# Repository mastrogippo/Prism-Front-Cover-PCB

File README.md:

## Front cover for Prism 

[Writeup and pics here](https://www.mastrogippo.it/2019/09/front-cover/)

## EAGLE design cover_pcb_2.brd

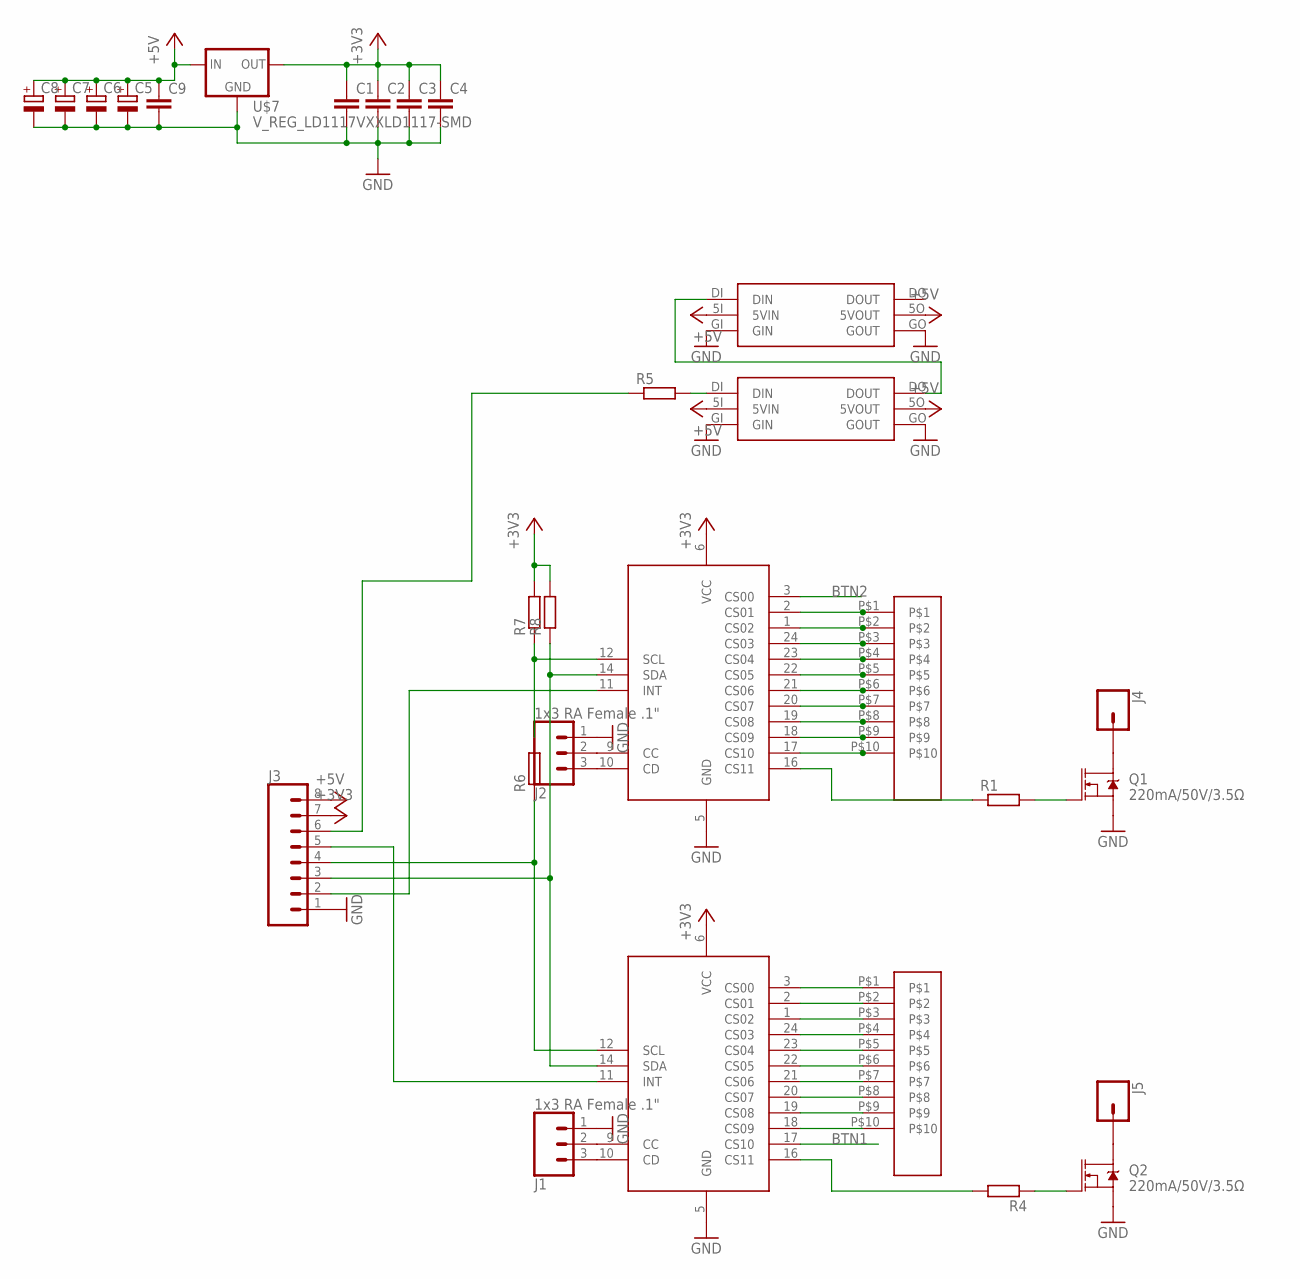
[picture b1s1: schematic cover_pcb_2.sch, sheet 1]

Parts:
C1, C2, C3, C4, C9: C-EUC0805K; C0805K
C5, C6, C7, C8: CPOL-EUSMCD; SMC_D
J1, J2: 1x3 RA Female .1"; 1X03_SMD_RA_FEMALE
J3: CONN_08SMD-MALE; 1X08_SMD_MALE
J4, J5: CONN_01SPRING-CONN; SPRING-CONNECTOR
Q1, Q2: 220mA/50V/3.5Ω; SOT23-3
R1, R4, R5, R6, R7, R8: R-EU_R0805; R0805
U$1, U$2: RGB6LED
U$3, U$4: TOUCH10; TOUCH10CM
U$5, U$6: CP112S; QSOP24
U$7: V_REG_LD1117VXXLD1117-SMD; SOT223

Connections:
+3V3: C1.1, C2.1, C3.1, C4.1, J3.7, R7.2, R8.2, U$5.6 (VCC), U$6.6 (VCC), U$7.2 (OUT)
+5V: C5.+, C6.+, C7.+, C8.+, C9.1, J3.8, U$1.5I (5VIN), U$1.5O (5VOUT), U$2.5I (5VIN), U$2.5O (5VOUT), U$7.3 (IN)
BTN1: U$6.17 (CS10)
BTN2: U$5.3 (CS00)
GND: C1.2, C2.2, C3.2, C4.2, C5.-, C6.-, C7.-, C8.-, C9.2, J1.1, J2.1, J3.1, Q1.2 (S), Q2.2 (S), U$1.GI (GIN), U$1.GO (GOUT), U$2.GI (GIN), U$2.GO (GOUT), U$5.5 (GND), U$6.5 (GND), U$7.1 (GND); also elsewhere on the board
unnamed: U$3.P$1, U$5.2 (CS01)
unnamed: U$3.P$2, U$5.1 (CS02)
unnamed: U$3.P$3, U$5.24 (CS03)
unnamed: U$3.P$4, U$5.23 (CS04)
unnamed: U$3.P$5, U$5.22 (CS05)
unnamed: U$3.P$6, U$5.21 (CS06)
unnamed: U$3.P$7, U$5.20 (CS07)
unnamed: U$3.P$8, U$5.19 (CS08)
unnamed: U$3.P$9, U$5.18 (CS09)
unnamed: U$4.P$1, U$6.3 (CS00)
unnamed: U$4.P$2, U$6.2 (CS01)
unnamed: U$4.P$3, U$6.1 (CS02)
unnamed: U$4.P$4, U$6.24 (CS03)
unnamed: U$4.P$5, U$6.23 (CS04)
unnamed: U$4.P$6, U$6.22 (CS05)
unnamed: U$4.P$7, U$6.21 (CS06)
unnamed: U$4.P$8, U$6.20 (CS07)
unnamed: U$4.P$9, U$6.19 (CS08)
unnamed: U$4.P$10, U$6.18 (CS09)
unnamed: R6.2, R7.1, U$5.12 (SCL)
unnamed: J3.5, U$6.11 (INT)
unnamed: U$1.DI (DIN), U$2.DO (DOUT)
unnamed: R1.1, U$5.16 (CS11)
unnamed: R4.2, U$6.16 (CS11)
unnamed: Q2.1 (G), R4.1
unnamed: J5.P$2, Q2.3 (D)
unnamed: R5.2, U$2.DI (DIN)
unnamed: J3.6, R5.1
unnamed: J3.3, R8.1, U$5.14 (SDA), U$6.14 (SDA)
unnamed: J3.4, R6.1, U$6.12 (SCL)
unnamed: J3.2, U$5.11 (INT)
unnamed: J4.P$2, Q1.3 (D)
unnamed: J2.2, U$5.9 (CC)
unnamed: J2.3, U$5.10 (CD)
unnamed: J1.2, U$6.9 (CC)
unnamed: J1.3, U$6.10 (CD)
unnamed: Q1.1 (G), R1.2
T1: U$3.P$10, U$5.17 (CS10)

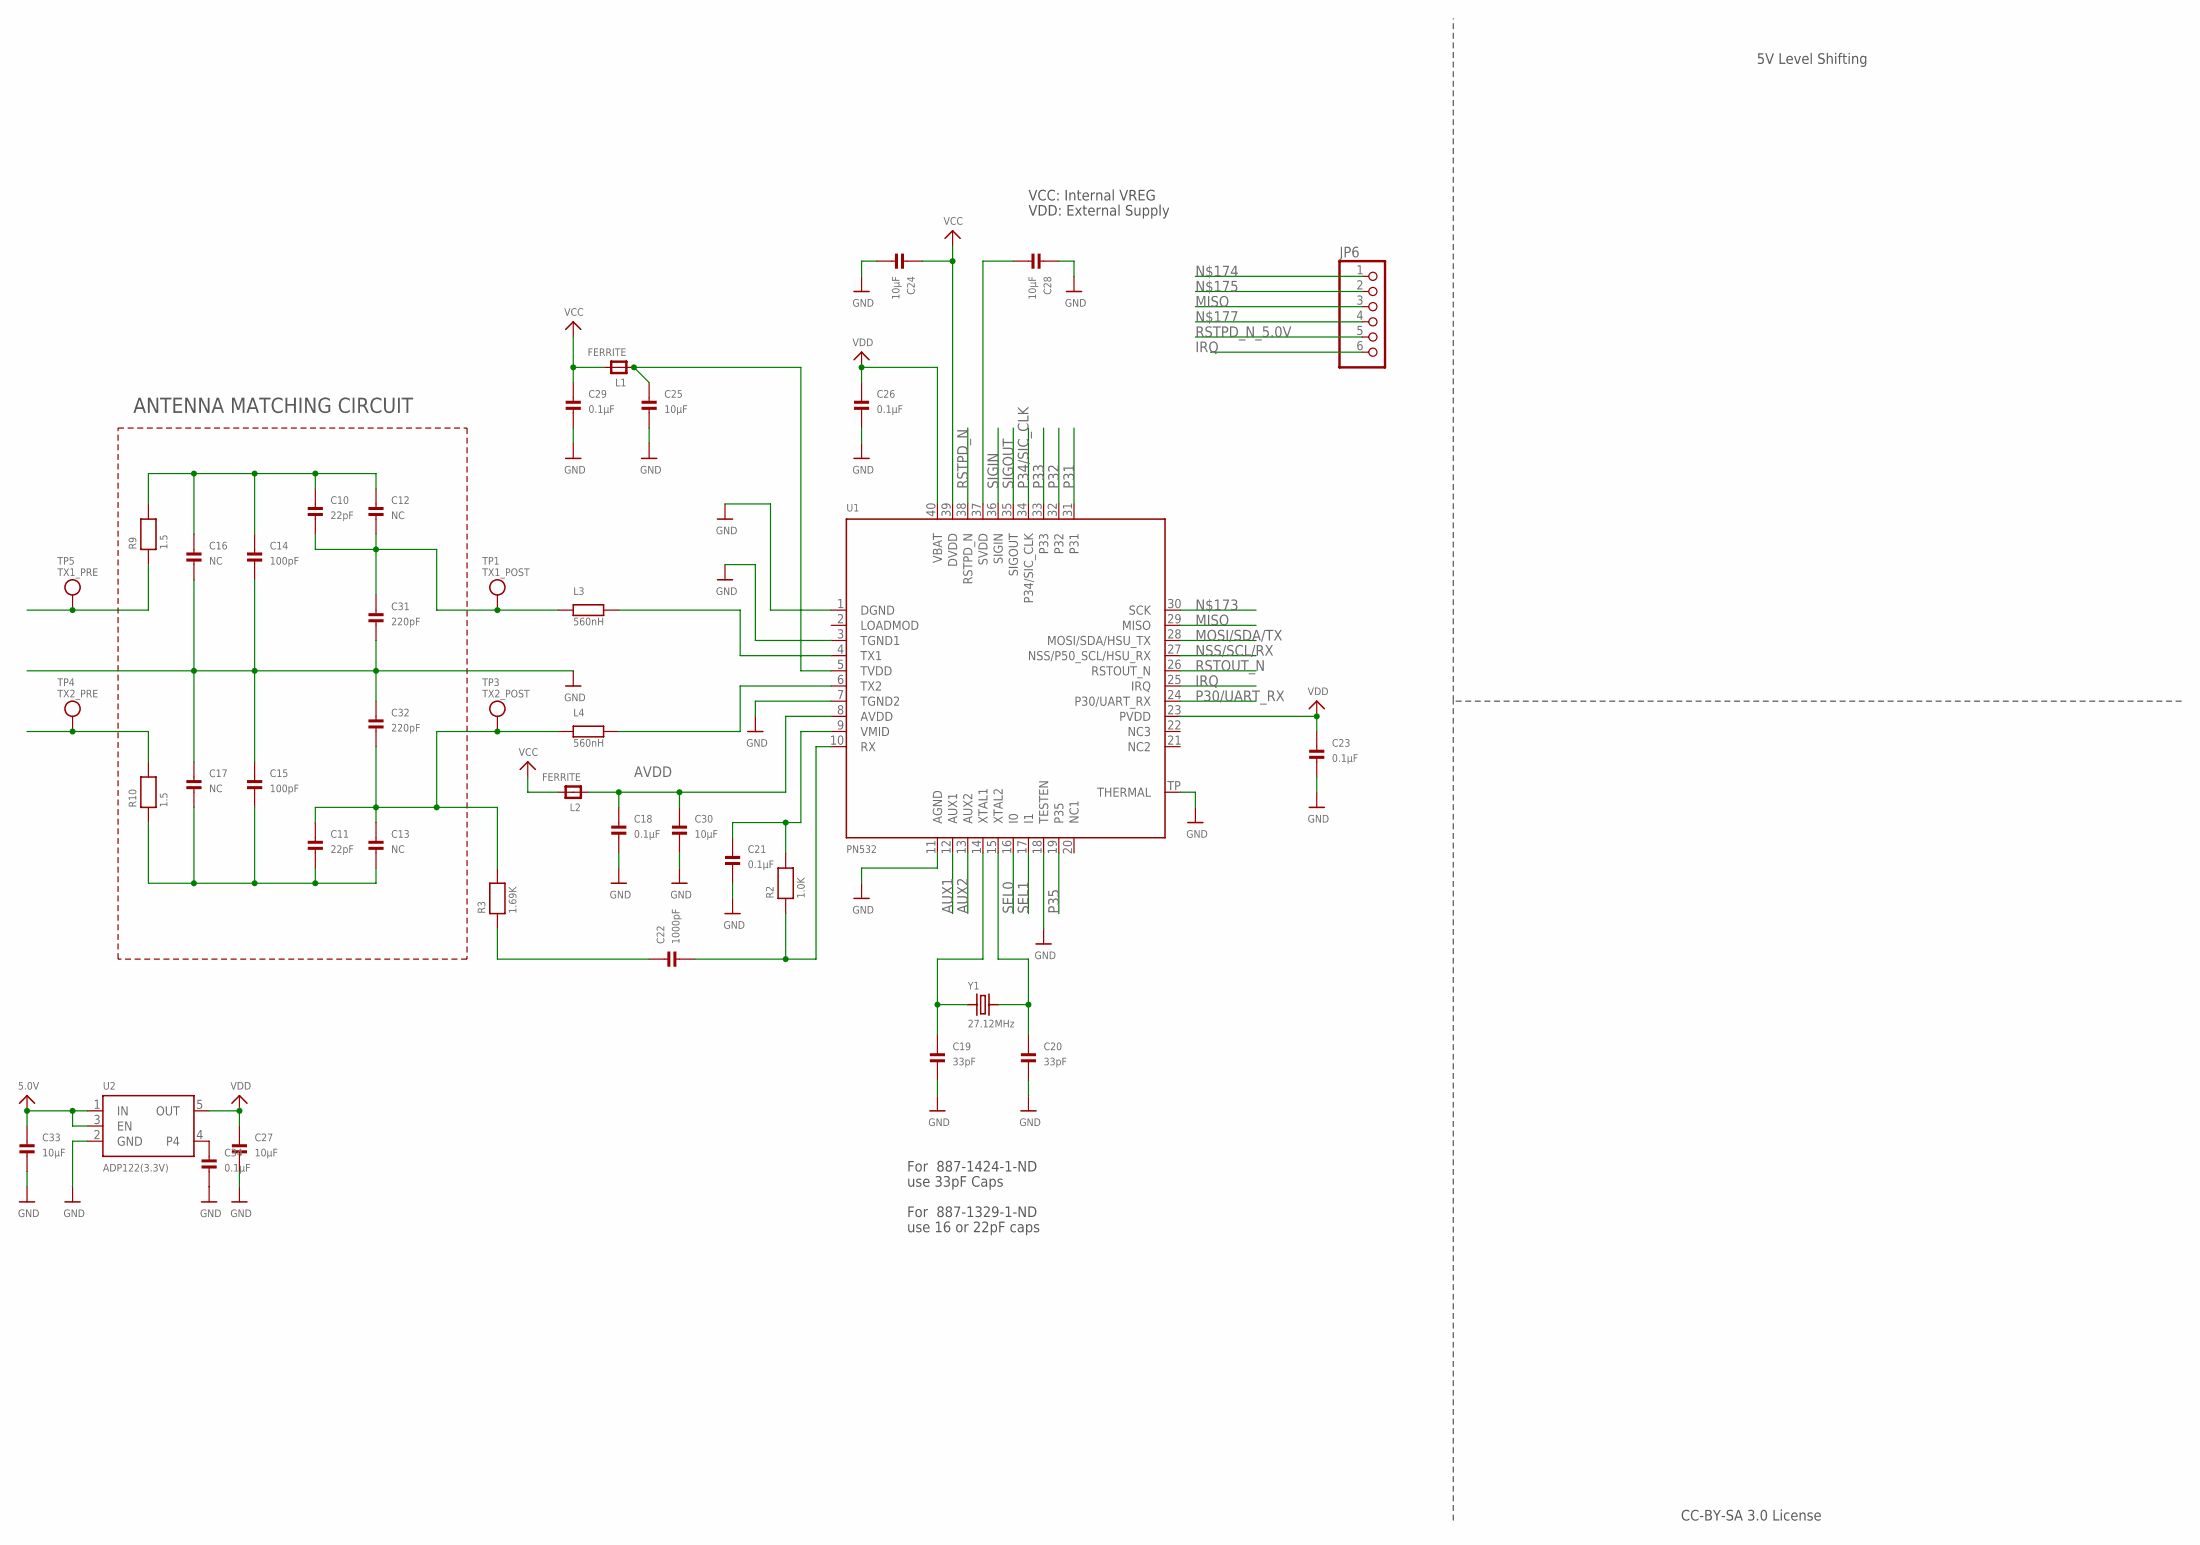
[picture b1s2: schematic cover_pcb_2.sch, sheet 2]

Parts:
C10, C11: 22pF; 0805
C12, C13, C16, C17: NC; 0805
C14, C15: 100pF; 0805
C18, C21, C23, C26, C29, C34: 0.1µF; 0805
C19, C20: 33pF; 0805
C22: 1000pF; 0805
C24, C25, C27, C28, C30, C33: 10µF; 0805
C31, C32: 220pF; 0805
JP6: PINHD-1X6B; 1X06-BIG
L1, L2: FERRITE; 0805
L3, L4: 560nH; R1206
R2: 1.0K; 0805
R3: 1.69K; 0805
R9, R10: 1.5; 0805
TP1: TX1_POST; TESTPOINT_PAD_2MM
TP3: TX2_POST; TESTPOINT_PAD_2MM
TP4: TX2_PRE; TESTPOINT_PAD_2MM
TP5: TX1_PRE; TESTPOINT_PAD_2MM
U1: PN532; HVQFN40-6X6
U2: ADP122(3.3V); SOT23-5
Y1: 27.12MHz; CRYSTAL_3.2X2.5

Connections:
5.0V: C33.1, U2.1 (IN), U2.3 (EN)
AUX1: U1.12 (AUX1)
AUX2: U1.13 (AUX2)
AVDD: C18.1, C30.1, L2.1, U1.8 (AVDD)
GND: C14.2, C15.1, C16.2, C17.1, C18.2, C19.2, C20.2, C21.2, C23.2, C24.2, C25.2, C26.2, C27.2, C28.1, C29.2, C30.2, C31.2, C32.1, C33.2, C34.2, U1.1 (DGND), U1.3 (TGND1), U1.7 (TGND2), U1.11 (AGND), U1.18 (TESTEN), U1.TP (THERMAL), U2.2 (GND); also elsewhere on the board
IRQ: JP6.6, U1.25 (IRQ)
MISO: JP6.3, U1.29 (MISO)
MOSI/SDA/TX: U1.28 (MOSI/SDA/HSU_TX)
unnamed: L3.2, U1.4 (TX1)
unnamed: L4.2, U1.6 (TX2)
unnamed: C10.2, C12.2, C31.1, L3.1, TP1.P$1
unnamed: C19.1, U1.14 (XTAL1), Y1.1
unnamed: C20.1, U1.15 (XTAL2), Y1.2
unnamed: C21.1, R2.2, U1.9 (VMID)
unnamed: C22.2, R2.1, U1.10 (RX)
unnamed: C22.1, R3.1
unnamed: C11.1, C13.1, C32.2, L4.1, R3.2, TP3.P$1
unnamed: R9.1, TP5.P$1
unnamed: R10.2, TP4.P$1
unnamed: C25.1, L1.1, U1.5 (TVDD)
unnamed: C34.1, U2.4
unnamed: C28.2, U1.37 (SVDD)
NSS/SCL/RX: U1.27 (NSS/P50_SCL/HSU_RX)
P30/UART_RX: U1.24 (P30/UART_RX)
P31: U1.31
P32: U1.32
P33: U1.33
P34/SIC_CLK: U1.34 (P34/SIC_CLK)
P35: U1.19 (P35)
RSTOUT_N: U1.26 (RSTOUT_N)
RSTPD_N: U1.38 (RSTPD_N)
RSTPD_N_5.0V: JP6.5
SEL0: U1.16 (I0)
SEL1: U1.17 (I1)
SIGIN: U1.36 (SIGIN)
SIGOUT: U1.35 (SIGOUT)
TX1_ANTENNA: C10.1, C12.1, C14.1, C16.1, R9.2
TX2_ANTENNA: C11.2, C13.2, C15.2, C17.2, R10.1
VCC: C24.1, C29.1, L1.2, L2.2, U1.39 (DVDD)
VDD: C23.1, C26.1, C27.1, U1.23 (PVDD), U1.40 (VBAT), U2.5 (OUT)

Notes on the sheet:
ANTENNA MATCHING CIRCUIT
CC-BY-SA 3.0 License
For 887-1329-1-ND
use 16 or 22pF caps
For 887-1424-1-ND
use 33pF Caps
5V Level Shifting
VCC: Internal VREG
VDD: External Supply

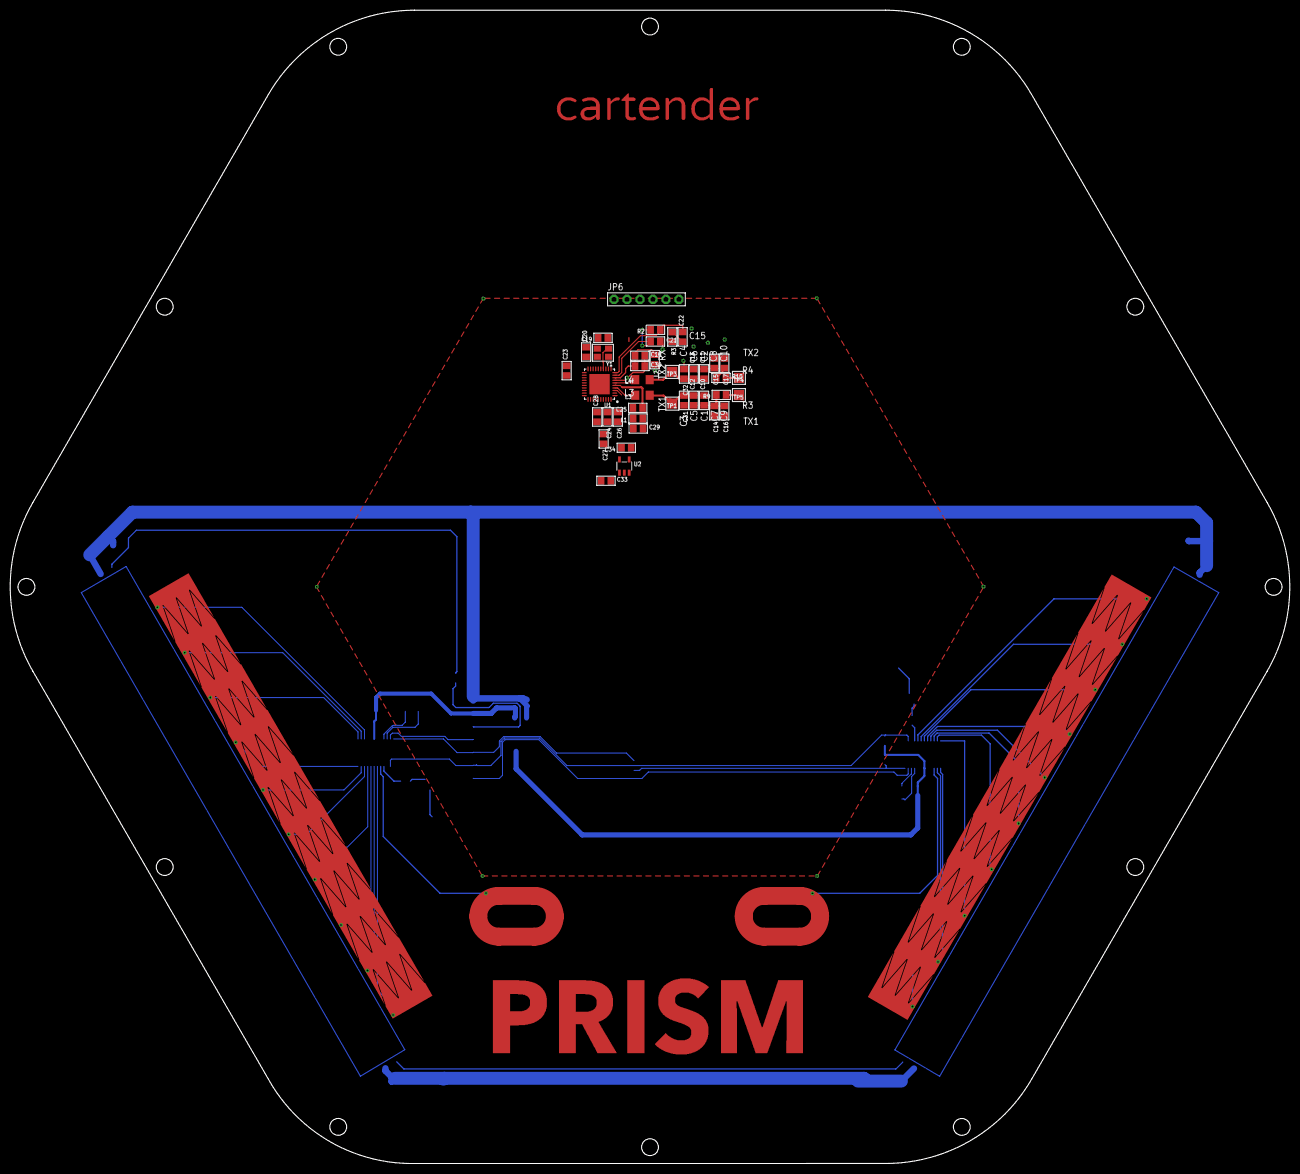
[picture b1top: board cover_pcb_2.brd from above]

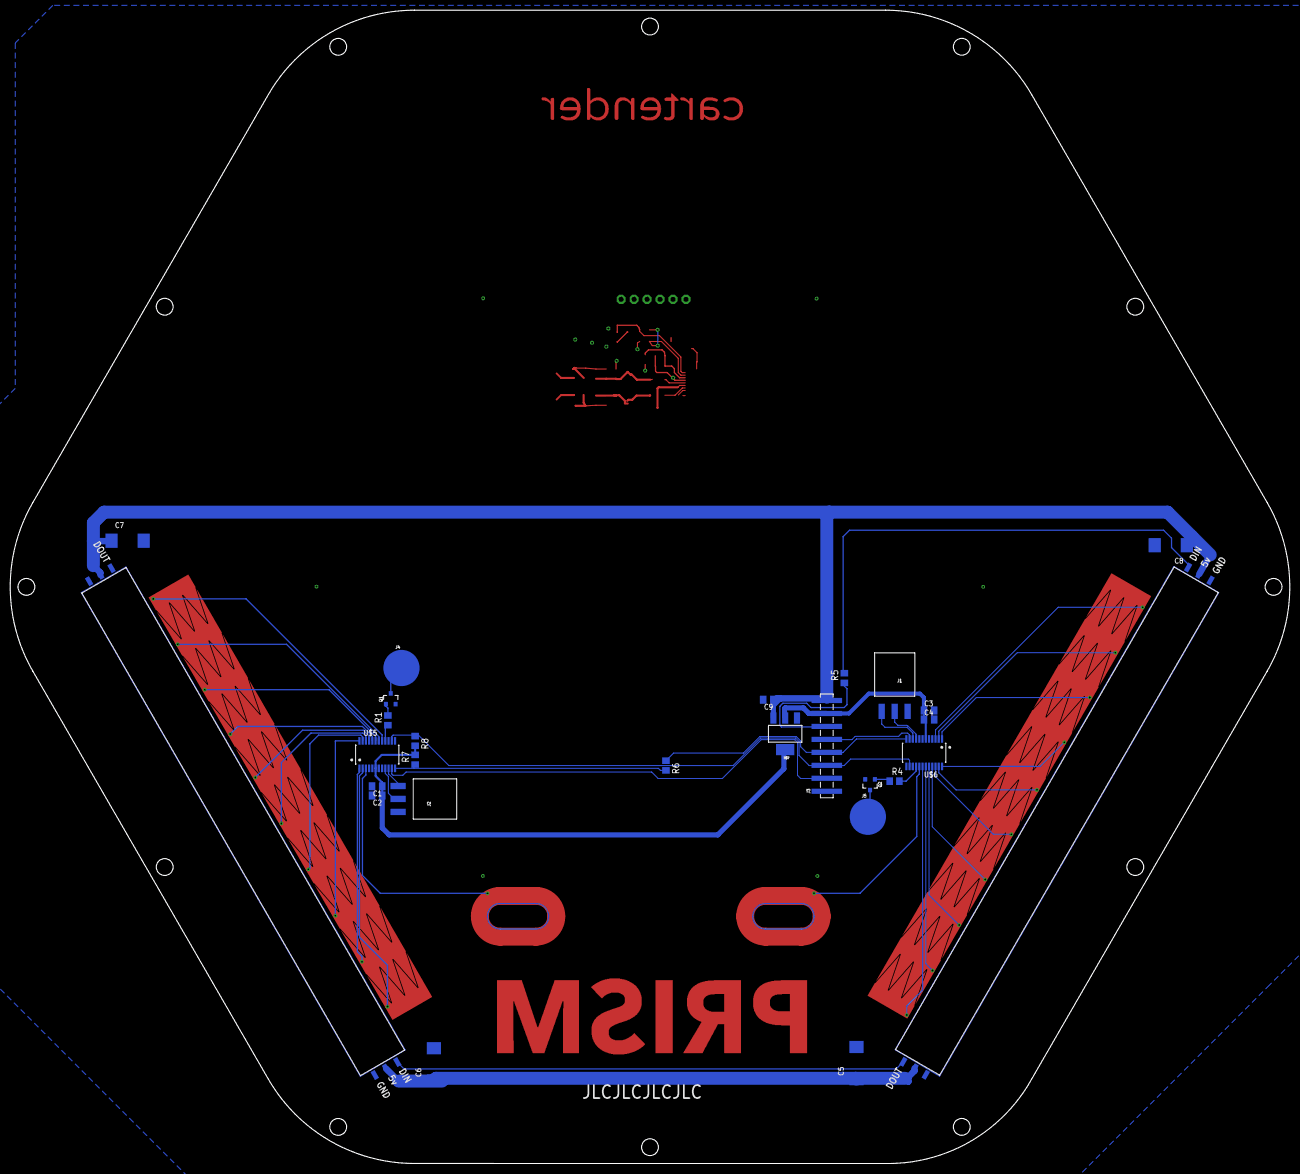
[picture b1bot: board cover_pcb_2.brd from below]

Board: 2 copper layers, 250.8 x 226.0 mm, 70 parts (25 on the bottom side), 63 nets.

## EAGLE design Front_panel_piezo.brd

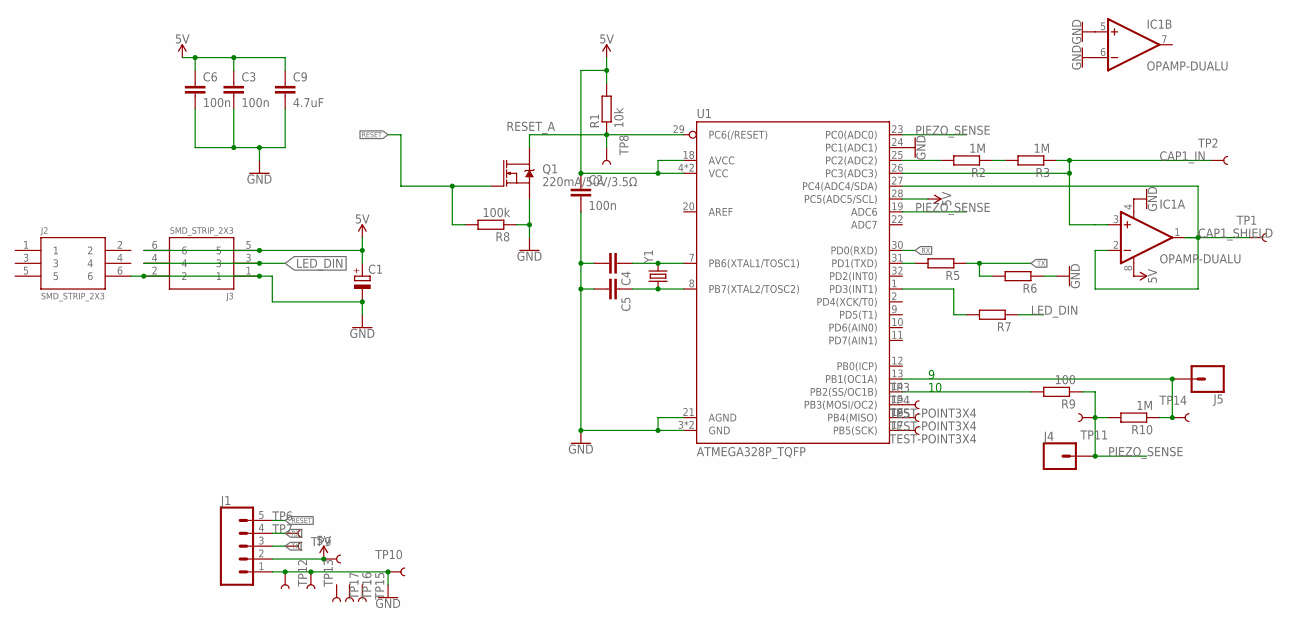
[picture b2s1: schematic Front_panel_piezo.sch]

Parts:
C1: CPOL-EUCT6032; CT6032
C2, C3, C6: 100n; C0805
C4, C5: C-EUC0805; C0805
C9: 4.7uF; C0805
IC1: OPAMP-DUALU; SO08
J1: CONN_05SMD2; 1X05_1MM_RA
J2, J3: SMD_STRIP_2X3
J4, J5: CONN_01SPRING-CONN; SPRING-CONNECTOR
Q1: 220mA/50V/3.5Ω; SOT23-3
R1: 10k; R0805
R2, R3, R10: 1M; R0805
R5, R6, R7: R-EU_R0805; R0805
R8: 100k; R0805
R9: 100; R0805
TP1, TP2, TP3, TP4, TP5, TP6, TP7, TP8, TP9, TP10, TP11, TP12, TP13, TP14, TP15, TP16, TP17: TEST-POINT3X4; PAD.03X.04
U1: ATMEGA328P_TQFP; TQFP32-08
Y1: CRYSTALSMD-3.2X2.5; CRYSTAL-SMD-3.2X2.5MM

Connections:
5V: C1.- (+), C2.1, C3.1, C6.1, C9.1, IC1.8 (V+), J1.2, J3.5, J3.6, R1.2, TP9.P$1, U1.4 (VCC), U1.6 (VCC), U1.18 (AVCC), U1.28 (PC5(ADC5/SCL))
CAP1_IN: IC1.3 (+IN), R3.1, TP2.P$1, U1.26 (PC3(ADC3))
CAP1_SHIELD: IC1.1 (OUT), IC1.2 (-IN), TP1.P$1, U1.27 (PC4(ADC4/SDA))
GND: C1.+ (-), C2.2, C3.2, C4.2, C5.2, C6.2, C9.2, IC1.4 (V-), IC1.5 (+IN), IC1.6 (-IN), J1.1, J2.6, J3.1, J3.2, Q1.2 (S), R6.1, R8.1, TP10.P$1, TP12.P$1, TP13.P$1, U1.3 (GND), U1.5 (GND), U1.21 (AGND), U1.24 (PC1(ADC1))
LED_DIN: J3.3, J3.4, R7.1
unnamed: R2.2, U1.25 (PC2(ADC2))
unnamed: R7.2, U1.1 (PD3(INT1))
unnamed: R2.1, R3.2
unnamed: C4.1, U1.7 (PB6(XTAL1/TOSC1)), Y1.3 (2)
unnamed: C5.1, U1.8 (PB7(XTAL2/TOSC2)), Y1.1
unnamed: R5.2, U1.31 (PD1(TXD))
unnamed: J5.P$2, R10.1, TP14.P$1, U1.13 (PB1(OC1A))
unnamed: R9.2, U1.14 (PB2(SS/OC1B))
unnamed: TP3.P$1, U1.15 (PB3(MOSI/OC2))
unnamed: TP4.P$1, U1.16 (PB4(MISO))
unnamed: TP5.P$1, U1.17 (PB5(SCK))
PIEZO_SENSE: J4.P$2, R9.1, R10.2, TP11.P$1, U1.19 (ADC6), U1.23 (PC0(ADC0))
RESET: J1.5, Q1.1 (G), R8.2
RESET_A: Q1.3 (D), R1.1, TP8.P$1, U1.29 (PC6(/RESET))
RX: J1.4, TP6.P$1, U1.30 (PD0(RXD))
TX: J1.3, R5.1, R6.2, TP7.P$1

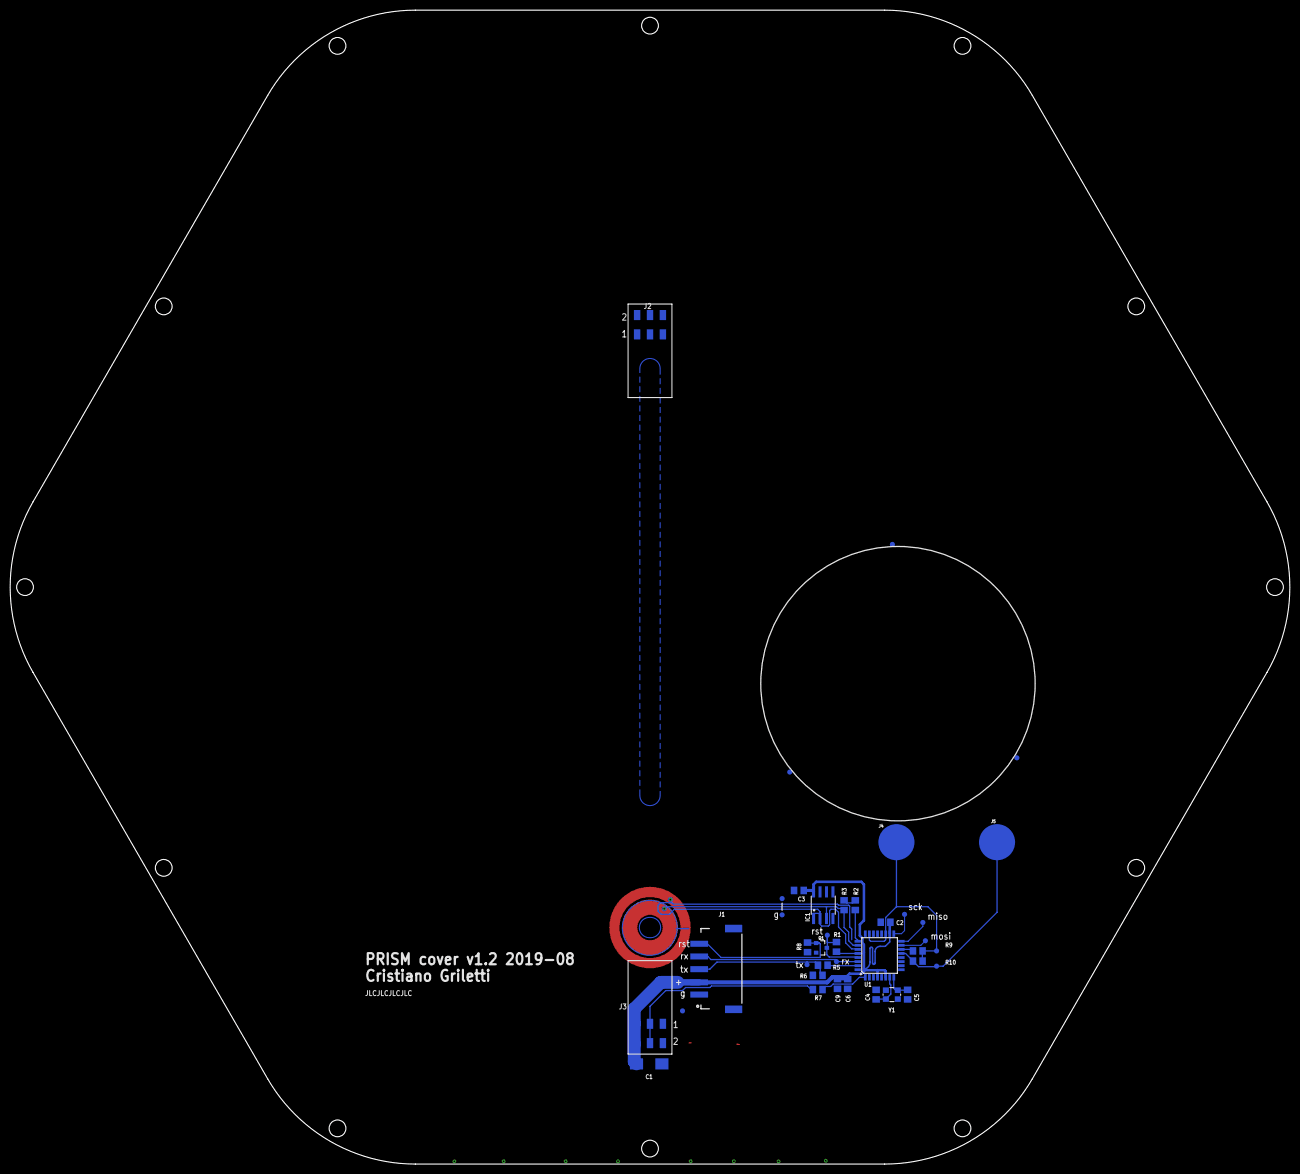
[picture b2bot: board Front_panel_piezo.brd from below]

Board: 2 copper layers, 251.8 x 227.1 mm, 42 parts (42 on the bottom side), 21 nets.

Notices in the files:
parts and their libraries:
SparkFun-IC-Microcontroller: Licensing: Creative Commons ShareAlike 4.0 International - https://creativecommons.org/licenses/by-sa/4.0
SparkFun: Licensing: CC v3.0 Share-Alike You are welcome to use this library for commercial purposes.
